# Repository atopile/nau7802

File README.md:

# nau7802

Wooohooo a new package!

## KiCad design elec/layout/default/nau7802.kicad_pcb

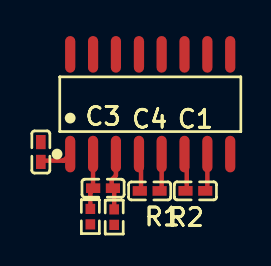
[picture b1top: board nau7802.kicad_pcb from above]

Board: 2 copper layers, 7 parts (0 on the bottom side), 7 nets.

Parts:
C1, C2, C3: 100nF ±10% 16V X7R; C0402-b3ef17
C4: 470pF ±10% 50V X7R; C0402-b3ef17
R1, R2: 51Ω ±1% 62.5mW; R0402-56259e
U1: SOP-16_L9.9-W3.9-P1.27-LS6.0-BL

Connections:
REFP: C2.1, U1.1
VBG: C1.1, U1.6
VIN1N: C3.1, R1.1, U1.2
VIN1P: C3.2, R2.1, U1.3
VIN2N: C4.1, U1.4
VIN2P: C4.2, U1.5
gnd: C1.2, C2.2, U1.7, U1.8, U1.9

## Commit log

2024-02-14 Configure project
2024-02-15 layout
2024-10-17 Add dual sensor build
2025-01-16 relink with 0.3 compiler
2025-04-05 update to kicad 9
2025-04-05 build with latest
